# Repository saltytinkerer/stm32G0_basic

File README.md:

# Basic development board for the STM32G070 Microcontroller.

This project contains KiCAD design files for a basic/simple and low cost STM32G070 (32-LQFP 0.8mm pitch variant) microcontroller development board. Components utilized are all larger easy to hand solder surface mount components. They're all mounted on the top side for easy access. 

For more information go to [this blog entry](http://www.saltytinkerer.com/post/stm32g070_dev_board/)

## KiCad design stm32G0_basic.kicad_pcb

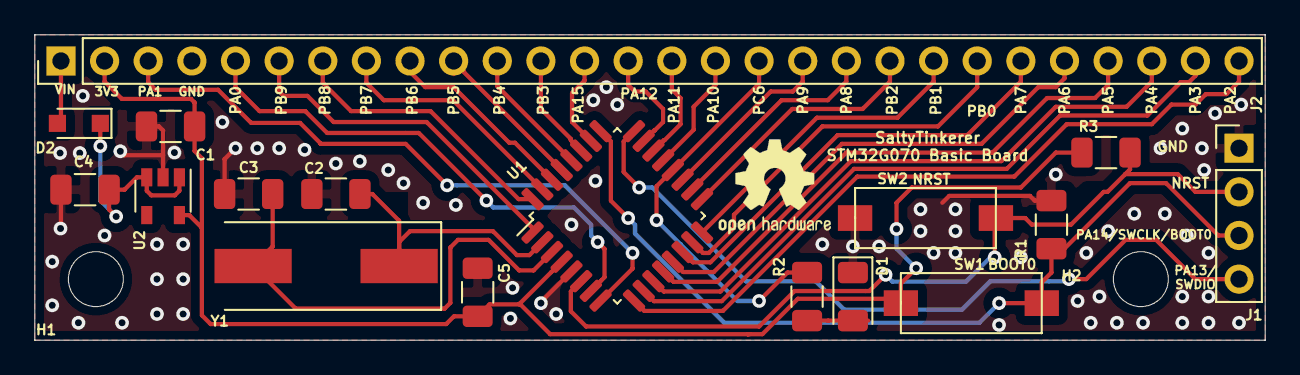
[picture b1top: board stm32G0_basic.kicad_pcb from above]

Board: 2 copper layers, 71.6 x 17.8 mm, 19 parts (0 on the bottom side), 35 nets.

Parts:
C1, C4, C5: 1u; C_1206_3216Metric
C2, C3: 22p; C_1206_3216Metric
D1: LED; LED_1206_3216Metric
D2: 1SS404,H3F; D_SOD-323_HandSoldering
H1, H2: MountingHole; MountingHole_3.2mm_M3
J1: Conn_01x04; PinHeader_1x04_P2.54mm_Vertical
J2: Conn_01x28; PinHeader_1x28_P2.54mm_Vertical
R1, R3: 10k; R_1206_3216Metric
R2: 330; R_1206_3216Metric
SW1, SW2: SW_Push; PTS636 SM43 SMTR LFS
U1: stm32G070KxTx; LQFP-32_7x7mm_P0.8mm
U2: MIC5504-3.3YM5; SOT-23-5
Y1: 8M; Crystal_SMD_HC49-SD

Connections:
+3V3: C1.1, C5.1, J2.2, R3.1, SW1.1, U1.4, U2.5
GND: C1.2, C2.1, C3.1, C4.2, C5.2, D1.1, J1.1, J2.4, R1.2, SW2.1, U1.5, U2.2
NRST: J1.2, R3.2, SW2.2, U1.6
unnamed: C2.2, U1.2, Y1.1
unnamed: C3.2, U1.3, Y1.2
unnamed: C4.1, D2.1, U2.1, U2.3
unnamed: D1.2, R2.2
PA0: J2.5, U1.7
PA1: J2.3, U1.8
PA2: J2.28, U1.9
PA3: J2.27, U1.10
PA4: J2.26, U1.11
PA5: J2.25, U1.12
PA6: J2.24, U1.13
PA7: J2.23, U1.14
PA8: J2.19, U1.18
PA9: J2.18, U1.19
PA10: J2.16, U1.21
PA11: J2.15, U1.22
PA12: J2.14, U1.23
PA13_SWDIO: J1.4, U1.24
PA14_SWCLK_BOOT0: J1.3, R1.1, SW1.2, U1.25
PA15: J2.13, U1.26
PB0: J2.22, U1.15
PB1: J2.21, U1.16
PB2: J2.20, U1.17
PB3: J2.12, U1.27
PB4: J2.11, U1.28
PB5: J2.10, U1.29
PB6: J2.9, U1.30
PB7: J2.8, U1.31
PB8: J2.7, U1.32
PB9: J2.6, U1.1
PC6: J2.17, R2.1, U1.20
VIN: D2.2, J2.1

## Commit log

2019-07-20 now adding all files
